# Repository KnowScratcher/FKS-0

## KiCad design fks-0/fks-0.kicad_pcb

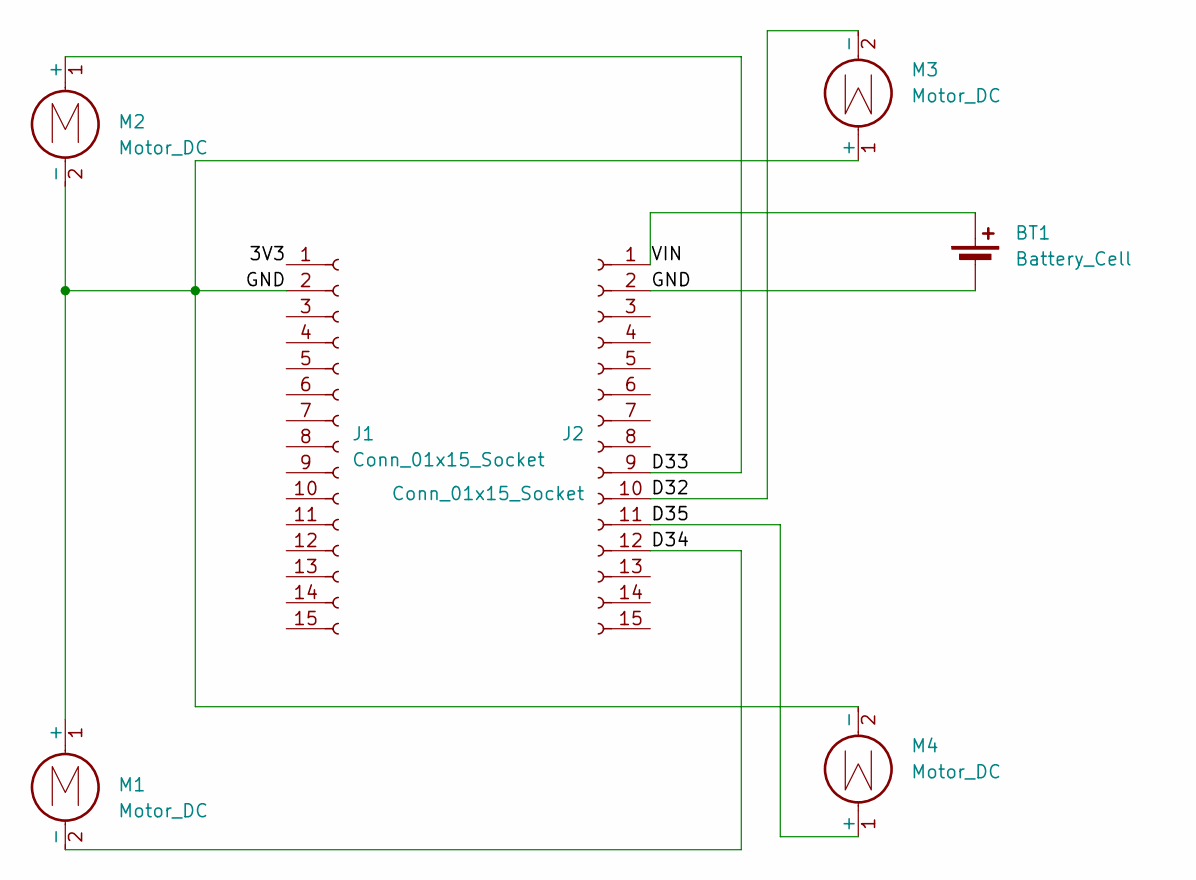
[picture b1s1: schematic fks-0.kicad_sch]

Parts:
BT1: Battery_Cell; SolderWire-0.15sqmm_1x02_P4mm_D0.5mm_OD1.5mm
J1, J2: Conn_01x15_Socket; PinSocket_1x15_P2.54mm_Vertical
M1, M2, M3, M4: Motor_DC; SolderWire-0.15sqmm_1x02_P4mm_D0.5mm_OD1.5mm

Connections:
/3V3: J1.1
/D32: J2.10, M3.2 (-)
/D33: J2.9, M2.1 (+)
/D34: J2.12, M1.2 (-)
/D35: J2.11, M4.1 (+)
/GND: BT1.2 (-), J1.2, J2.2, M1.1 (+), M2.2 (-), M3.1 (+), M4.2 (-)
/VIN: BT1.1 (+), J2.1

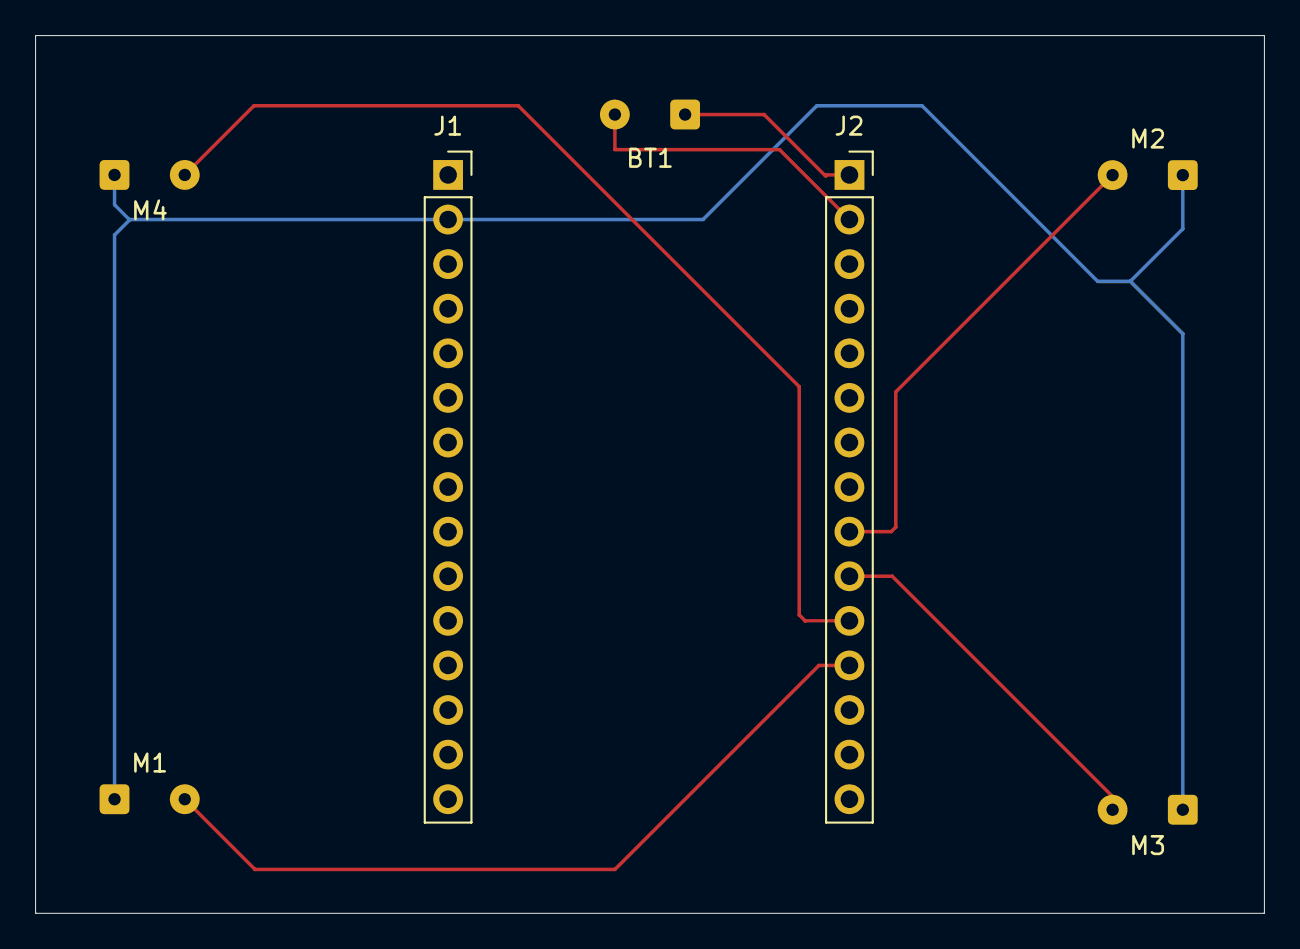
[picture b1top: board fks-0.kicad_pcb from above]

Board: 2 copper layers, 70.0 x 50.0 mm, 7 parts (0 on the bottom side), 6 nets.

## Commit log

2025-06-02 init
2025-06-02 update hour spent
2025-06-05 add journal
2025-06-08 fix journal
